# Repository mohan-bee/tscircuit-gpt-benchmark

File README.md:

# PCB Bench

A minimal benchmark viewer for comparing the same AI-generated circuit across tscircuit and KiCad. Filter by model and complexity, then switch both tool columns between PCB and schematic snapshots.

The tscircuit column embeds the RunFrame preview with PCB, schematic, 3D, assembly, pinout, BOM, Circuit JSON, and error tabs, plus its File menu and fullscreen control. It loads the saved benchmark output without exposing a code tab. PCB and schematic selections stay synchronized with the comparison tabs; other RunFrame views stay within the tscircuit column.

## Run locally

```bash
npm install
npm run dev
```

## Verify

```bash
npm test
npm run build
```

Regenerate every snapshot from its committed source with:

```bash
./scripts/render-snapshots.sh
```

The KiCad images are generated locally with KiCad CLI 10.0.1. See `AGENTS.md` for the no-placeholder snapshot policy and verification workflow.

## Add a model run

Copy `benchmark-template/benchmark.json` to `src/benchmarks/<run-id>/benchmark.json`, add the available native sources and generated snapshots under `public/benchmarks/<run-id>/`, and fill in the exact model, prompt, complexity, circuit, and renderer versions. Mark an unavailable platform as pending so its column stays empty. The dashboard discovers the run and builds its filters automatically.

See [CONTRIBUTING.md](CONTRIBUTING.md) for the file layout, renderer commands, and validation checklist.

## Automatic scoring and model comparisons

Run fixed, versioned prompts against multiple models, build both native CAD formats, and score objective checks out of 100. See [the benchmark runner guide](benchmarks/README.md) for setup, metrics, replay, provenance, and comparison rules. No AI judges are used.

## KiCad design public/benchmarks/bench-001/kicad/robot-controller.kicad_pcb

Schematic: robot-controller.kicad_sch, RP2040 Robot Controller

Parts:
C1, C4, C5, C6, C7, C8, C9, C10, C11, C12, C23, C24: 100n; C_0603_1608Metric
C2, C3: 15p; C_0603_1608Metric
C13, C14, C25: 1u; C_0603_1608Metric
C15, C16: 4.7u; C_0603_1608Metric
C17, C20: 100n 50V; C_0603_1608Metric
C18, C21: 10u 25V; C_1206_3216Metric
C19, C22: 100u 25V; CP_Elec_6.3x7.7
C26: 100u 10V; CP_Elec_6.3x7.7
D1: USBLC6-2SC6; SOT-23-6
D2, D3: SS14; D_SMA
H1, H2, H3, H4: M2.5; MountingHole_2.7mm_M2.5
J1: USB-C; USB_C_Receptacle_HRO_TYPE-C-31-M-12
J2: VM 7-12V; PinHeader_1x02_P2.54mm_Vertical
J3: M1 OUTPUT; PinHeader_1x02_P2.54mm_Vertical
J4: M2 OUTPUT; PinHeader_1x02_P2.54mm_Vertical
J5: ENC1 3V3 G A B; PinHeader_1x04_P2.54mm_Vertical
J6: ENC2 3V3 G A B; PinHeader_1x04_P2.54mm_Vertical
J7: SERVO1 S V G; PinHeader_1x03_P2.54mm_Vertical
J8: SERVO2 S V G; PinHeader_1x03_P2.54mm_Vertical
J9: SERVO3 S V G; PinHeader_1x03_P2.54mm_Vertical
J10: SWD / GND; PinHeader_1x03_P2.54mm_Vertical
J11: 5V LOGIC IN; PinHeader_1x02_P2.54mm_Vertical
J12: SERVO 5-6V IN; PinHeader_1x02_P2.54mm_Vertical
J13: GPIO / I2C; PinHeader_1x10_P2.54mm_Vertical
R1, R3, R18, R20, R22, R24: 10k; R_0603_1608Metric
R2, R4, R17, R19, R21, R23: 1k; R_0603_1608Metric
R5, R6: 5.1k; R_0603_1608Metric
R7, R8: 27; R_0603_1608Metric
R9, R12: 64.9k; R_0603_1608Metric
R10, R11, R13, R14: 100k; R_0603_1608Metric
R15, R16: 4.7k; R_0603_1608Metric
SW1: RESET; SW_SPST_TL3342
SW2: BOOT; SW_SPST_TL3342
U1: RP2040; QFN-56-1EP_7x7mm_P0.4mm_EP3.2x3.2mm
U2: W25Q16JVSSIQ; SOIC-8_5.3x5.3mm_P1.27mm
U3: AP2112K-3.3; SOT-23-5
U4, U5: DRV8871DDA; Texas_HTSOP-8-1EP_3.9x4.9mm_P1.27mm_EP2.95x4.9mm_Mask2.4x3.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
U6: LSM6DS3; LGA-14_3x2.5mm_P0.5mm_LayoutBorder3x4y
Y1: 12MHz 10pF; Crystal_SMD_3225-4Pin_3.2x2.5mm

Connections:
/1V1: C11.1, C12.1, C14.1, U1.23 (DVDD), U1.45 (VREG_VOUT), U1.50 (DVDD)
/3V3: C1.1, C4.1, C5.1, C6.1, C7.1, C8.1, C9.1, C10.1, C13.1, C16.1, C23.1, C24.1, C25.1, J5.1, J6.1, J13.1, R1.1, R3.1, R15.1, R16.1, R18.1, R20.1, R22.1, R24.1, U1.1 (IOVDD), U1.10 (IOVDD), U1.22 (IOVDD), U1.33 (IOVDD), U1.42 (IOVDD), U1.43 (ADC_AVDD), U1.44 (VREG_VIN), U1.48 (USB_VDD), U1.49 (IOVDD), U2.8 (VCC), U3.5 (VOUT), U6.5 (VDDIO), U6.8 (VDD), U6.12 (CS)
/BOOT_SW: R4.2, SW2.1
/CC1: J1.A5 (CC1), R5.1
/CC2: J1.B5 (CC2), R6.1
/E1A: J5.3, R17.1
/E1B: J5.4, R19.1
/E2A: J6.3, R21.1
/E2B: J6.4, R23.1
/ENC1_A: R17.2, R18.2, U1.6 (GPIO4)
/ENC1_B: R19.2, R20.2, U1.7 (GPIO5)
/ENC2_A: R21.2, R22.2, U1.8 (GPIO6)
/ENC2_B: R23.2, R24.2, U1.9 (GPIO7)
/EXT_5V: D3.2 (A), J11.1
/GND: C1.2, C2.2, C3.2, C4.2, C5.2, C6.2, C7.2, C8.2, C9.2, C10.2, C11.2, C12.2, C13.2, C14.2, C15.2, C16.2, C17.2, C18.2, C19.2, C20.2, C21.2, C22.2, C23.2, C24.2, C25.2, C26.2, D1.2 (GND), J1.A1 (GND), J1.A12 (GND), J1.B1 (GND), J1.B12 (GND), J1.SH (SHIELD), J2.2, J5.2, J6.2, J7.3, J8.3, J9.3, J10.2, J11.2, J12.2, J13.2, R5.2, R6.2, R9.2, R10.2, R11.2, R12.2, R13.2, R14.2, SW1.2, SW2.2, U1.19 (TESTEN), U1.57 (GND), U2.4 (GND), U3.2 (GND), U4.1 (GND), U4.7 (GND), U4.9 (GND), U5.1 (GND), U5.7 (GND), U5.9 (GND), U6.1 (SDO/SA0), U6.6 (GND), U6.7 (GND), Y1.2 (G), Y1.4 (G)
/GPIO14: J13.3, U1.17 (GPIO14)
/GPIO15: J13.4, U1.18 (GPIO15)
/GPIO16: J13.5, U1.27 (GPIO16)
/GPIO17: J13.6, U1.28 (GPIO17)
/GPIO26: J13.7, U1.38 (GPIO26/ADC0)
/GPIO27: J13.8, U1.39 (GPIO27/ADC1)
/I2C_SCL: J13.10, R16.2, U1.12 (GPIO9), U6.13 (SCL)
/I2C_SDA: J13.9, R15.2, U1.11 (GPIO8), U6.14 (SDA)
/IMU_INT: U1.16 (GPIO13), U6.4 (INT1)
/LOGIC_5V: C15.1, D2.1 (K), D3.1 (K), U3.1 (VIN), U3.3 (EN)
/M1_ILIM: R9.1, U4.4 (ILIM)
/M1_IN1: R10.1, U1.2 (GPIO0), U4.3 (IN1)
/M1_IN2: R11.1, U1.3 (GPIO1), U4.2 (IN2)
/M1_OUT1: J3.1, U4.6 (OUT1)
/M1_OUT2: J3.2, U4.8 (OUT2)
/M2_ILIM: R12.1, U5.4 (ILIM)
/M2_IN1: R13.1, U1.4 (GPIO2), U5.3 (IN1)
/M2_IN2: R14.1, U1.5 (GPIO3), U5.2 (IN2)
/M2_OUT1: J4.1, U5.6 (OUT1)
/M2_OUT2: J4.2, U5.8 (OUT2)
/QSPI_CLK: U1.52 (QSPI_SCLK), U2.6 (CLK)
/QSPI_CS: R1.2, R4.1, U1.56 (~QSPI_SS), U2.1 (~CS)
/QSPI_D0: U1.53 (QSPI_SD0), U2.5 (DI/IO_{0})
/QSPI_D1: U1.55 (QSPI_SD1), U2.2 (DO/IO_{1})
/QSPI_D2: U1.54 (QSPI_SD2), U2.3 (~WP/IO_{2})
/QSPI_D3: U1.51 (QSPI_SD3), U2.7 (~HOLD/~RESET/IO_{3})
/RUN: R3.2, SW1.1, U1.26 (RUN)
/SERVO1: J7.1, U1.13 (GPIO10)
/SERVO2: J8.1, U1.14 (GPIO11)
/SERVO3: J9.1, U1.15 (GPIO12)
/SWCLK: J10.3, U1.24 (SWCLK)
/SWDIO: J10.1, U1.25 (SWDIO)
/USB_DM: R7.2, U1.46 (USB_DM)
/USB_DP: R8.2, U1.47 (USB_DP)
/USB_M: D1.1 (I/O1), D1.6 (I/O1), J1.A7 (D-), J1.B7 (D-), R7.1
/USB_P: D1.3 (I/O2), D1.4 (I/O2), J1.A6 (D+), J1.B6 (D+), R8.1
/VBUS: D1.5 (VBUS), D2.2 (A), J1.A4 (VBUS), J1.A9 (VBUS), J1.B4 (VBUS), J1.B9 (VBUS)
/VM: C17.1, C18.1, C19.1, C20.1, C21.1, C22.1, J2.1, U4.5 (VM), U5.5 (VM)
/VSERVO: C26.1, J7.2, J8.2, J9.2, J12.1
/XIN: C2.1, U1.20 (XIN), Y1.1
/XOUT: R2.1, U1.21 (XOUT)
/XTAL_OUT: C3.1, R2.2, Y1.3

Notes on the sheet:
RP2040 / QSPI / CLOCK
USB-C / 3.3V LOGIC
DUAL MOTOR DRIVERS / VM 7-12V
6-AXIS IMU / I2C 0x6A
ENCODERS / SERVOS / EXPANSION
70 x 60 mm / 2-layer / common GND plane
USB powers logic only. External VM and VSERVO required. Encoder / GPIO signals: 3.3V only.

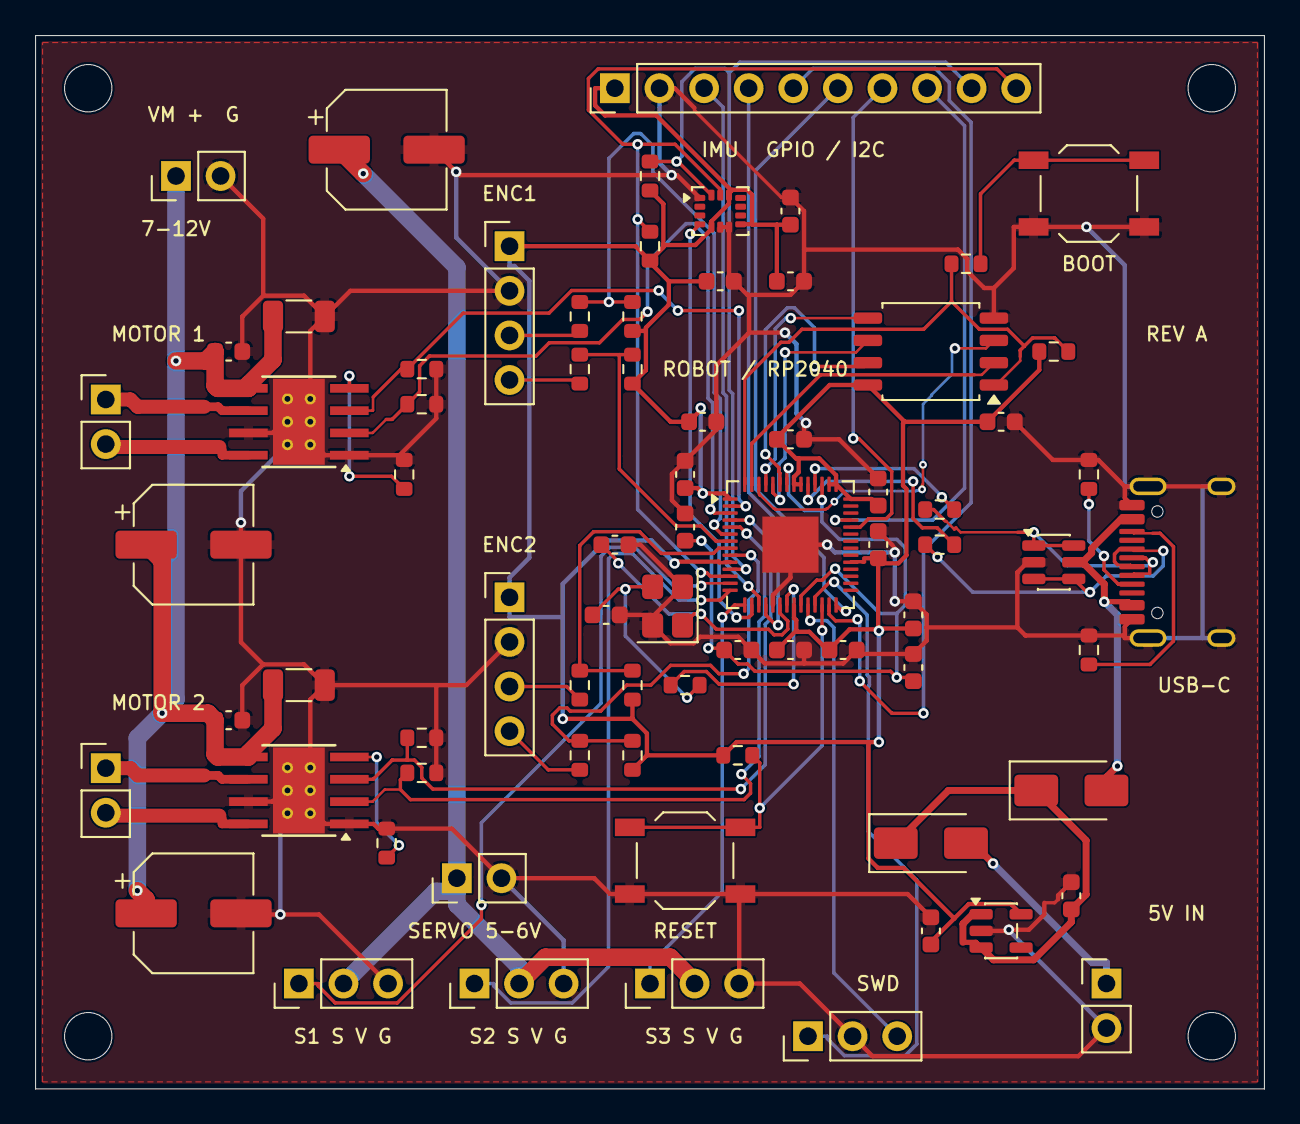
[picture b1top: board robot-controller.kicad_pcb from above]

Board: 2 copper layers, 70.0 x 60.0 mm, 79 parts (0 on the bottom side), 57 nets.

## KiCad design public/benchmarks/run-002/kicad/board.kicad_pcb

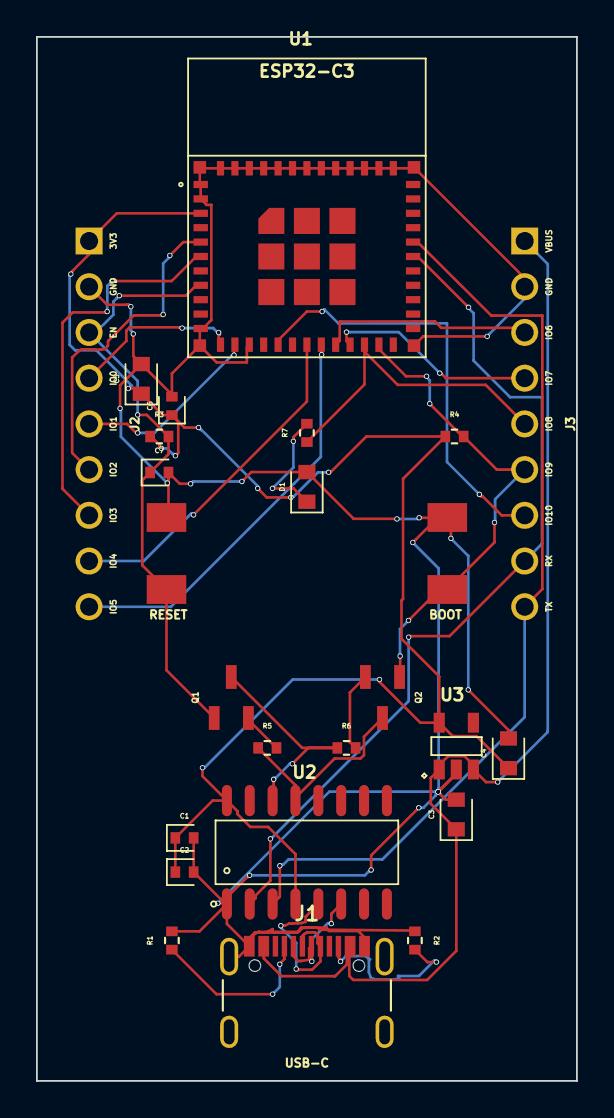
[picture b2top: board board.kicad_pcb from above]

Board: 2 copper layers, 30.0 x 58.0 mm, 25 parts (0 on the bottom side), 26 nets.

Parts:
C1, C2, C6: 100nF; capacitor_cap0402
C3, C4, C5: 10uF; capacitor_cap0603
C7: 1uF; capacitor_cap0402
D1: LED; led_0603_color(green)
J1: J1; USB4105-GF-A
J2: J2; pin_header_pinrow9_p2.54_female
J3: J3; pin_header_pinrow9_p2.54_female
Q1: Q1; transistor_sot23
Q2: Q2; transistor_sot23
R1, R2: 5.1kΩ; resistor_res0402
R3, R4, R5, R6: 10kΩ; resistor_res0402
R7: 1kΩ; resistor_res0402
SW1: SW1; push_button
SW2: SW2; push_button
U1: ESP32-C3-MINI-1-N4
U2: CH340C
U3: AP2112K-3.3TRG1

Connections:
.J1 > .pin3 to .R1 > .pin1: J1.3, R1.1
.J1 > .pin11 to .R2 > .pin1: J1.11, R2.1
.J2 > .pin4 to .U1 > .IO0: J2.4, U1.12
.J2 > .pin5 to .U1 > .IO1: J2.5, U1.13
.J2 > .pin6 to .U1 > .IO2: J2.6, U1.5
.J2 > .pin7 to .U1 > .IO3: J2.7, U1.6
.J2 > .pin8 to .U1 > .IO4: J2.8, U1.18
.J2 > .pin9 to .U1 > .IO5: J2.9, U1.19
.J3 > .pin3 to .U1 > .IO6: J3.3, U1.20
.J3 > .pin4 to .U1 > .IO7: J3.4, U1.21
.J3 > .pin7 to .U1 > .IO10: J3.7, U1.16
.R5 > .pin2 to .Q1 > .base: Q1.2, R5.2
.R6 > .pin2 to .Q2 > .base: Q2.2, R6.2
.R7 > .pin2 to .D1 > .anode: D1.1, R7.2
.U1 > .IO8 to .R7 > .pin1: J3.5, R7.1, U1.22
.U2 > .RXD to .U1 > .TXD0: J3.9, U1.31, U2.3
.U2 > .TXD to .U1 > .RXD0: J3.8, U1.30, U2.2
DTR_N: Q2.3, R5.1, U2.13
EN: C7.1, J2.3, Q1.1, R3.2, SW1.1, U1.8
GND: C1.2, C2.2, C3.2, C4.2, C5.2, C6.2, C7.2, D1.2, J1.1, J1.8, J1.9, J1.16, J1.17, J2.2, J3.2, R1.2, R2.2, SW1.2, SW2.2, U1.1, U1.2, U1.11, U1.14, U1.36, U1.37, U1.38, U1.39, U1.40, U1.41, U1.42, U1.43, U1.44, U1.45, U1.46, U1.47, U1.48, U1.50, U1.51, U1.52, U1.53, U2.1, U3.2
IO9: J3.6, Q2.1, R4.2, SW2.1, U1.23
RTS_N: Q1.3, R6.1, U2.14
USB_DM: J1.5, J1.13, U2.6
USB_DP: J1.4, J1.12, U2.5
VBUS: C3.1, J1.2, J1.7, J1.10, J1.15, J3.1, U3.1, U3.3
VCC_3V3: C1.1, C2.1, C4.1, C5.1, C6.1, J2.1, R3.1, R4.1, U1.3, U2.4, U2.16, U3.5

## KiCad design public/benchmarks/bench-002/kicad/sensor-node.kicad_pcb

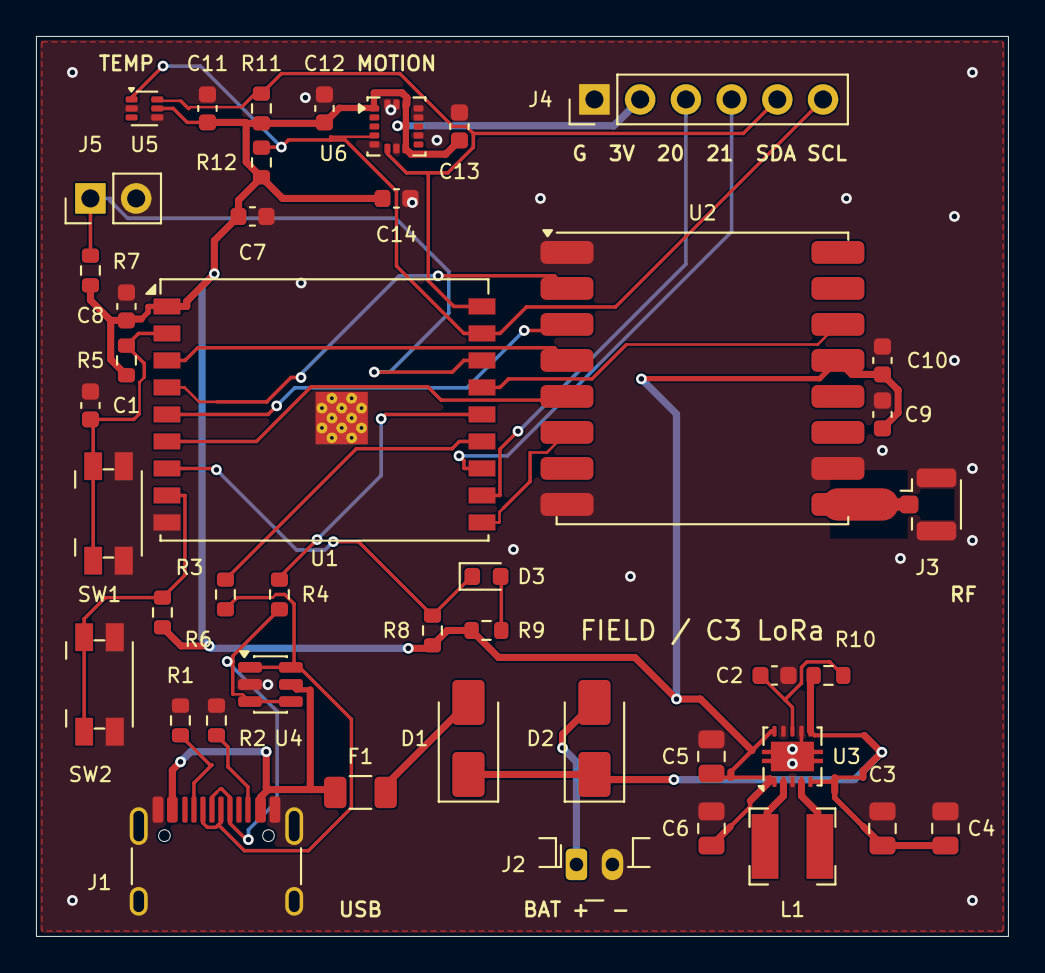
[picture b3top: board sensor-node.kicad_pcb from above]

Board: 2 copper layers, 54.0 x 50.0 mm, 44 parts (0 on the bottom side), 31 nets.

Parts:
C1, C13: 1uF 10V; C_0603_1608Metric
C2, C8, C10, C11, C12, C14: 100nF 10V; C_0603_1608Metric
C3, C4: 10uF 10V X7R; C_0805_2012Metric
C5, C6: 22uF 10V X5R; C_0805_2012Metric
C7, C9: 10uF 10V; C_0603_1608Metric
D1, D2: SS24; D_SMA
D3: GREEN; LED_0603_1608Metric
F1: 0.5A hold; Fuse_1206_3216Metric
J1: USB-C / USB2; USB_C_Receptacle_HRO_TYPE-C-31-M-12
J2: BAT 1S protected; JST_PH_S2B-PH-K_1x02_P2.00mm_Horizontal
J3: LoRa ANT 50R; U.FL_Hirose_U.FL-R-SMT-1_Vertical
J4: GPIO / I2C; PinHeader_1x06_P2.54mm_Vertical
J5: STRAP GPIO2; PinHeader_1x02_P2.54mm_Vertical
L1: 2.2uH / SRN4018-2R2M; L_Bourns-SRN4018
R1, R2: 5.1k; R_0603_1608Metric
R3, R4: 22; R_0603_1608Metric
R5, R6, R7, R8: 10k; R_0603_1608Metric
R9: 1k; R_0603_1608Metric
R10: 100; R_0603_1608Metric
R11, R12: 4.7k; R_0603_1608Metric
SW1: RESET; Panasonic_EVQPUJ_EVQPUA
SW2: BOOT; Panasonic_EVQPUJ_EVQPUA
U1: ESP32-C3-WROOM-02U-N4; ESP32-C3-WROOM-02U
U2: RFM95W-868S2; HOPERF_RFM9XW_SMD
U3: TPS63001DRCR; Texas_DRC0010J
U4: USBLC6-2SC6; SOT-23-6
U5: TMP102AIDRLR; SOT-563
U6: LIS3DHTR; LGA-16_3x3mm_P0.5mm_LayoutBorder3x5y

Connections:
+3V3: C5.1, C6.1, C7.1, C8.1, C9.1, C10.1, C11.1, C12.1, C13.1, C14.1, J4.2, R5.1, R6.1, R7.1, R8.1, R9.1, R11.1, R12.1, U1.1, U2.13, U3.1, U3.10, U5.5, U6.1, U6.8, U6.14
BOOT: R6.2, SW2.1, U1.8
CC1: J1.A5, R1.1
CC2: J1.B5, R2.1
EN: C1.1, R5.2, SW1.1, U1.2
GND: C1.2, C2.2, C3.2, C4.2, C5.2, C6.2, C7.2, C8.2, C9.2, C10.2, C11.2, C12.2, C13.2, C14.2, J1.A1, J1.A12, J1.B1, J1.B12, J1.SH, J2.2, J3.2, J4.1, J5.2, R1.2, R2.2, SW1.2, SW2.2, U1.9, U1.19, U2.1, U2.8, U2.10, U3.3, U3.7, U3.9, U3.11, U4.2, U5.2, U5.4, U6.5, U6.7, U6.10, U6.12, U6.13, U6.15, U6.16
GPIO2: J5.1, R7.2, U1.16
GPIO20: J4.3, U1.11
GPIO21: J4.4, U1.12
LED_A: D3.2, R9.2
LED_GPIO8: D3.1, R8.2, U1.7
LORA_CS: U1.6, U2.5
LORA_IRQ: U1.15, U2.14
LORA_RST: U1.10, U2.6
MISO: U1.4, U2.2
MOSI: U1.5, U2.3
RF_ANT: J3.1, U2.9
SCK: U1.3, U2.4
SCL: J4.6, R12.2, U1.17, U5.1, U6.4
SDA: J4.5, R11.2, U1.18, U5.6, U6.6
SW1: L1.2, U3.4
SW2: L1.1, U3.2
USB_DM: R3.2, U1.13
USB_DM_CONN: J1.A7, J1.B7, R3.1, U4.1, U4.6
USB_DP: R4.2, U1.14
USB_DP_CONN: J1.A6, J1.B6, R4.1, U4.3, U4.4
USB_FUSED: D1.2, F1.2
VBAT: D2.2, J2.1
VBUS: F1.1, J1.A4, J1.A9, J1.B4, J1.B9, U4.5
VINA: C2.1, R10.2, U3.8
VSYS: C3.1, C4.1, D1.1, D2.1, R10.1, U3.5, U3.6

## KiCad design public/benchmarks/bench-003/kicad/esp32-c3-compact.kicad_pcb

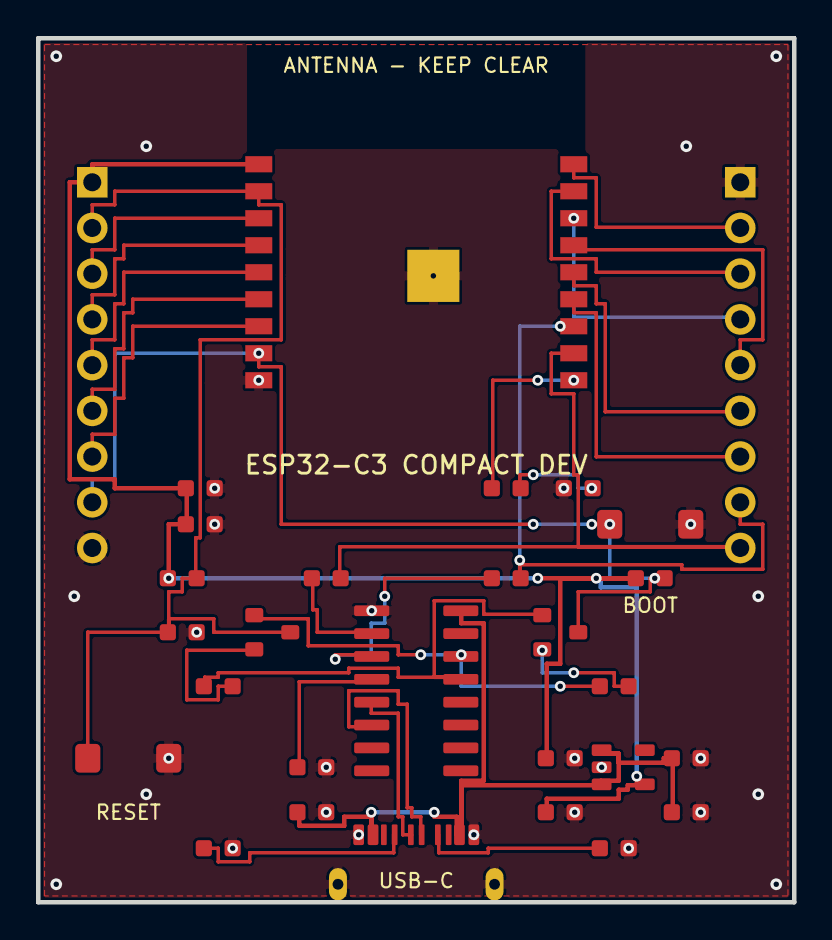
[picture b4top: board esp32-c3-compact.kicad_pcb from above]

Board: 2 copper layers, 42.0 x 48.0 mm, 29 parts (0 on the bottom side), 31 nets.

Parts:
C1: 10uF; Custom_C1_C_0603_1608Metric.
C2: 100nF; Custom_C2_C_0603_1608Metric.
C3: 10uF; Custom_C3_C_0603_1608Metric.
C4: 100nF; Custom_C4_C_0603_1608Metric.
C5: 100nF; Custom_C5_C_0603_1608Metric.
C6: 100nF; Custom_C6_C_0603_1608Metric.
C7: 100nF; Custom_C7_C_0603_1608Metric.
C8: 10uF; Custom_C8_C_0603_1608Metric.
C9: 1uF; Custom_C9_C_0603_1608Metric.
D1: STATUS GREEN; Custom_D1_LED_0603_1608Metric
J1: USB-C POWER/PROGRAM; Custom_J1_USB_C_Receptacle_GCT_USB4105-xx-A_16P_TopMnt_Hori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
J2: GPIO HEADER; Custom_J2_PinHeader_1x09_P2.54mm_Vertical
J3: GPIO HEADER; Custom_J3_PinHeader_1x09_P2.54mm_Vertical
Q1: MMBT3904; Custom_Q1_SOT-23
Q2: MMBT3904; Custom_Q2_SOT-23
R1: 5.1k; Custom_R1_R_0603_1608Metric.
R2: 5.1k; Custom_R2_R_0603_1608Metric.
R3: 470R; Custom_R3_R_0603_1608Metric.
R4: 470R; Custom_R4_R_0603_1608Metric.
R5: 10k; Custom_R5_R_0603_1608Metric.
R6: 10k; Custom_R6_R_0603_1608Metric.
R7: 10k; Custom_R7_R_0603_1608Metric.
R8: 10k; Custom_R8_R_0603_1608Metric.
R9: 1k; Custom_R9_R_0603_1608Metric.
SW1: RESET; Custom_SW1_SW_SPST_TL3342
SW2: BOOT; Custom_SW2_SW_SPST_TL3342
U1: ESP32-C3-WROOM-02; Custom_U1_ESP32-C3-WROOM-02
U2: CH340C; Custom_U2_SOIC-16_3.9x9.9mm_P1.27mm
U3: AP2112K-3.3; Custom_U3_SOT-23-5

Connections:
3V3: C3.1, C4.1, C7.1, C8.1, J2.1, R7.1, R8.1, U1.1, U3.5
CC1: J1.A5, R1.1
CC2: J1.B5, R2.1
CH340_V3: C5.1, U2.4
DTR: Q2.2, R5.1, U2.13
DTR_B: Q1.1, R5.2
EN: C9.1, J2.2, Q1.3, R7.2, SW1.1, U1.2
GND: C1.2, C2.2, C3.2, C4.2, C5.2, C6.2, C7.2, C8.2, C9.2, D1.1, J1.A1, J1.A12, J1.B1, J1.B12, J1.SH, J2.9, J3.1, R1.2, R2.2, SW1.2, SW2.2, U1.9, U1.19, U2.1, U3.2
IO0: J3.2, U1.18
IO1: J3.3, U1.17
IO2: J3.4, U1.16
IO3: J3.5, U1.15
IO4: J2.3, U1.3
IO5: J2.4, U1.4
IO6: J2.5, U1.5
IO7: J2.6, U1.6
IO8: J2.7, U1.7
IO9_BOOT: J2.8, Q2.3, R8.2, SW2.1, U1.8
IO10_LED: R9.1, U1.10
IO18: J3.7, U1.13
IO19: J3.6, U1.14
IO20_RXD: J3.9, R3.2, U1.11
IO21_TXD: J3.8, R4.2, U1.12
LED_A: D1.2, R9.2
RTS: Q1.2, R6.1, U2.14
RTS_B: Q2.1, R6.2
UART_RX: R4.1, U2.3
UART_TX: R3.1, U2.2
USB_DM: J1.A7, J1.B7, U2.6
USB_DP: J1.A6, J1.B6, U2.5
VBUS: C1.1, C2.1, C6.1, J1.A4, J1.A9, J1.B4, J1.B9, U2.16, U3.1, U3.3
